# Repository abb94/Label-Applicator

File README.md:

# 🏷️ Automated Label Applicator

The goal for this project is to make a cheap and automated DIY Label Applicator for small bottles and flasks with adjustable size, relative to the bottle placed on the device. 

---

## 📚 Table of Contents

- [Introduction](#-introduction)
- [Requirements](#-requirements)
- [Features](#-features)
- [Hardware](#-hardware)
- [Software](#-software)
- [Installation](#-installation)
- [Design Files](#-design-files)
- [Roadmap](#-roadmap)
- [Log](#-log)
- [Learnings](#-learnings)

---

## 🔍 Introduction

This project was created for a friend who is passionate about honey farming. In 2024, his bee colonies produced nearly half a ton of honey. Since each bottle contains roughly half a kilo, that’s about 1,000 bottles to label by hand — a task that’s both time-consuming and far from the most enjoyable part of beekeeping. Commercial automatic label applicators are notoriously expensive, so this project aims to develop a more affordable alternative.

---

## ‼️: Requirements

- [ ] Easy to move around. 
- [ ] Apply labels on different dimensions of glass and label sizes. 
- [ ] Easy to maintain.
- [ ] Easy to use.
- [ ] Semi-automatic and manual to operate. 

---

## ✨ Features

<!-- List the features, for example: automatic feed, sensor detection, calibration, etc. -->

---

## 🔩 Hardware

- 2 x 20 mm x 20 mm x 60 mm I-type profiles
- 3 x 20 mm x 20 mm x 15 mm I-type profiles

---

## 🧠 Software

<!-- Describe the software architecture, languages, frameworks, and any libraries used. -->

---

## ⚙️ Installation

<!-- Step-by-step guide to installing and running the project. Include wiring diagrams or schematics if relevant. -->

---

## 🖼️ Design Files

Current socket design: <br>

---
### 📄: Learnings
- Create a component as the first thing in Fusion 360. Create the body, and the sketch creating that body, and keep it inside the component.
- Tolerances are difficult on a 3d Printer.
- Standardize as much as possible, and don't create several parts from one origin, that fits a niche purpose. It is easier to have the original modified so that it coveres all requirements. 

---

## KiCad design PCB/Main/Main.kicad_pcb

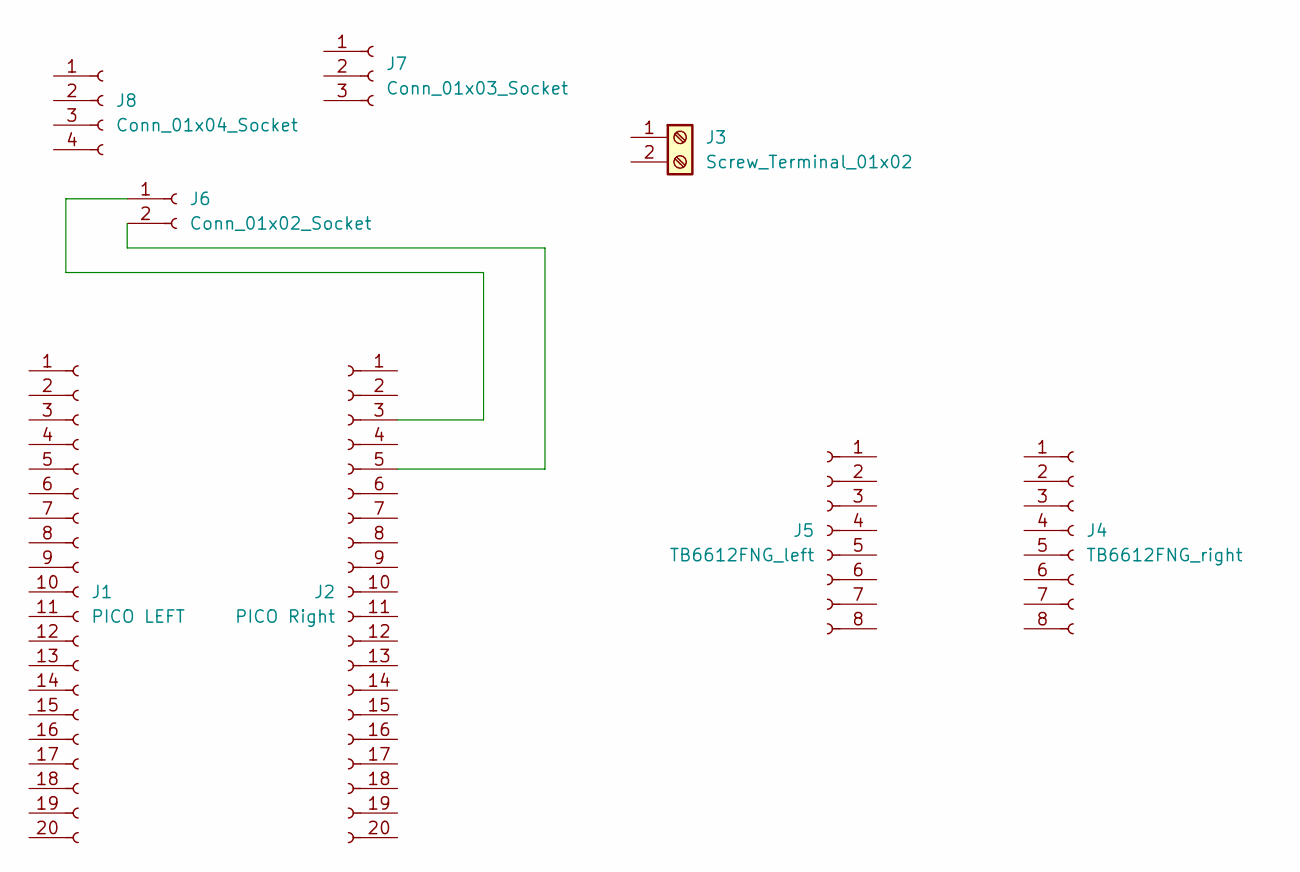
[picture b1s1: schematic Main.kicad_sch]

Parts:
J1: PICO LEFT; PinSocket_1x20_P2.54mm_Vertical
J2: PICO Right; PinSocket_1x20_P2.54mm_Vertical
J3: Screw_Terminal_01x02; TerminalBlock_MetzConnect_Type073_RT02602HBLU_1x02_P5.08mm_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
J4: TB6612FNG_right; PinSocket_1x08_P2.54mm_Vertical
J5: TB6612FNG_left; PinSocket_1x08_P2.54mm_Vertical
J6: Conn_01x02_Socket; JST_XH_B2B-XH-A_1x02_P2.50mm_Vertical
J7: Conn_01x03_Socket; JST_XH_B3B-XH-A_1x03_P2.50mm_Vertical
J8: Conn_01x04_Socket; JST_XH_B4B-XH-A_1x04_P2.50mm_Vertical

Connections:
unnamed: J2.3, J6.1
unnamed: J2.5, J6.2

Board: 2 copper layers, 8 parts (0 on the bottom side), 2 nets, no tracks yet.

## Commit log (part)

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2025-08-02 Create Framing_Socket_Sketch.dxf
    Tilføjelse af sketch til profil
2025-08-17 Added pictures and maintained library.
    Added pictures and maintained library.
2026-02-08 TIlføjelse af filer.
    TIlføjelse af filer.
2026-02-27 checkin.
2026-02-27 test
2026-02-27 slettes python ting.
2026-02-28 PCB editing
    changes to footprints.
2026-02-28 PLACED TB6612FNG Motor driver on schematic.
